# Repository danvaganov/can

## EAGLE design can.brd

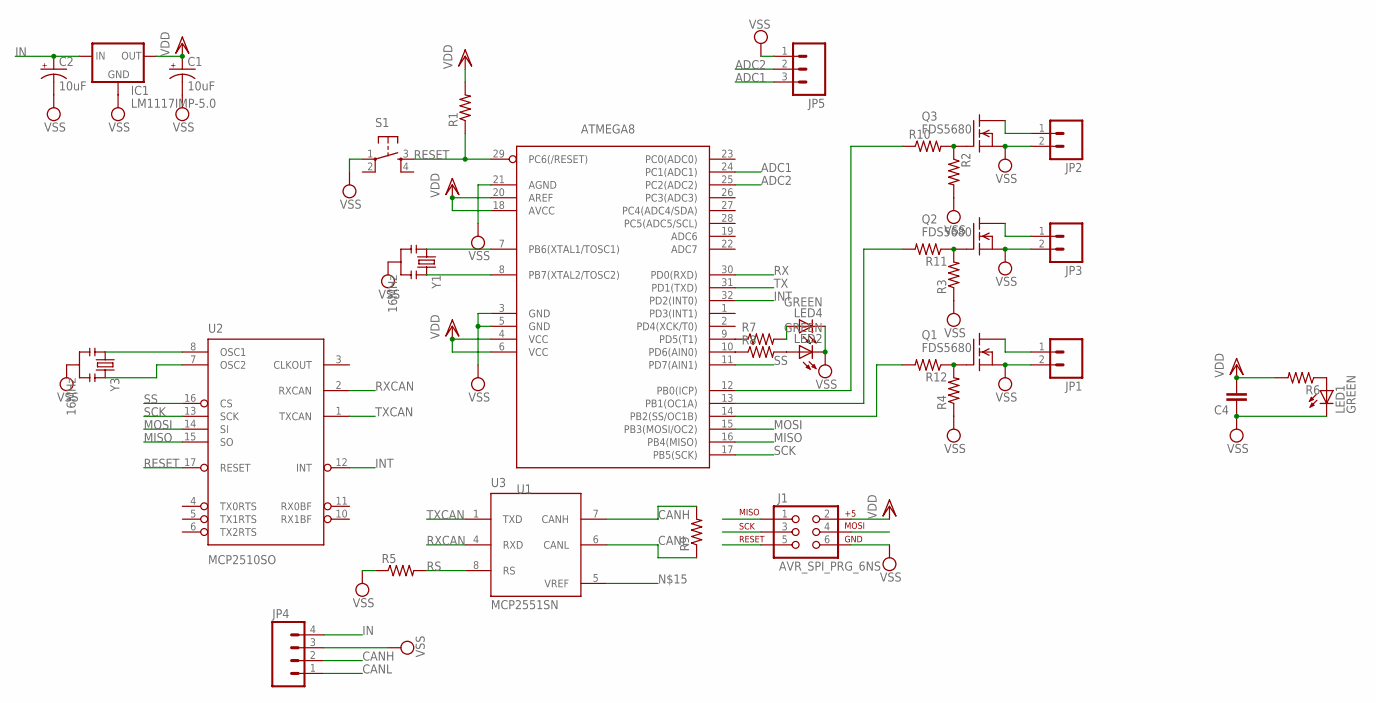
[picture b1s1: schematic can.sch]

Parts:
C1, C2: 10uF; EIA3216
C4: CAP1206; 1206
IC1: LM1117IMP-5.0; SOT223
J1: AVR_SPI_PRG_6NS; 2X3-NS
JP1, JP2, JP3: M02PTH; 1X02
JP4: M041X04_NO_SILK; 1X04_NO_SILK
JP5: M03PTH; 1X03
LED1, LED2, LED4: GREEN; LED-1206
Q1, Q2, Q3: FDS5680; SO-8
R1, R2, R3, R4, R5, R6, R9, R10, R11, R12: RESISTOR1206; 1206
R7, R8: RESISTOR0805-RES; 0805
S1: TAC_SWITCHSMD; TACTILE_SWITCH_SMD
U1: ATMEGA8; TQFP32-08
U2: MCP2510SO; SO-18W
U3: MCP2551SN; SO-08
Y1, Y3: 16MHz; RESONATOR-SMD

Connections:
ADC1: JP5.3, U1.24 (PC1(ADC1))
ADC2: JP5.2, U1.25 (PC2(ADC2))
CANH: JP4.2, R9.2, U3.7 (CANH)
CANL: JP4.1, R9.1, U3.6 (CANL)
IN: C2.A (+), IC1.3 (IN), JP4.4
INT: U1.32 (PD2(INT0)), U2.12 (INT)
MISO: J1.1, U1.16 (PB4(MISO)), U2.15 (SO)
MOSI: J1.4, U1.15 (PB3(MOSI/OC2)), U2.14 (SI)
unnamed: R8.1, U1.10 (PD6(AIN0))
unnamed: JP1.1, Q1.5 (D), Q1.6 (D), Q1.7 (D), Q1.8 (D)
unnamed: R7.1, U1.9 (PD5(T1))
unnamed: Q3.4 (G), R2.1, R10.2
unnamed: Q2.4 (G), R3.2, R11.1
unnamed: JP3.1, Q2.5 (D), Q2.6 (D), Q2.7 (D), Q2.8 (D)
unnamed: R12.2, U1.14 (PB2(SS/OC1B))
unnamed: JP2.1, Q3.5 (D), Q3.6 (D), Q3.7 (D), Q3.8 (D)
unnamed: Q1.4 (G), R4.2, R12.1
unnamed: R11.2, U1.13 (PB1(OC1A))
unnamed: R10.1, U1.12 (PB0(ICP))
unnamed: U1.7 (PB6(XTAL1/TOSC1)), Y1.1
unnamed: LED1.A, R6.1
unnamed: U1.8 (PB7(XTAL2/TOSC2)), Y1.3
unnamed: U2.8 (OSC1), Y3.1
unnamed: LED2.A, R8.2
unnamed: LED4.A, R7.2
unnamed: U2.7 (OSC2), Y3.3
RESET: J1.5, R1.1, S1.3, U1.29 (PC6(/RESET)), U2.17 (RESET)
RS: R5.2, U3.8 (RS)
RX: U1.30 (PD0(RXD))
RXCAN: U2.2 (RXCAN), U3.4 (RXD)
SCK: J1.3, U1.17 (PB5(SCK)), U2.13 (SCK)
SS: U1.11 (PD7(AIN1)), U2.16 (CS)
TX: U1.31 (PD1(TXD))
TXCAN: U2.1 (TXCAN), U3.1 (TXD)
VDD: C1.A (+), C4.2, IC1.2 (OUT), J1.2, R1.2, R6.2, U1.4 (VCC), U1.6 (VCC), U1.18 (AVCC), U1.20 (AREF), U2.18 (VDD), U3.3 (VDD)
VSS: C1.C (-), C2.C (-), C4.1, IC1.1 (GND), J1.6, JP1.2, JP2.2, JP3.2, JP4.3, JP5.1, LED1.C, LED2.C, LED4.C, Q1.1 (S), Q1.2 (S), Q1.3 (S), Q2.1 (S), Q2.2 (S), Q2.3 (S), Q3.1 (S), Q3.2 (S), Q3.3 (S), R2.2, R3.1, R4.1, R5.1, S1.1, U1.3 (GND), U1.5 (GND), U1.21 (AGND), U2.9 (VSS), U3.2 (VSS), Y1.2, Y3.2

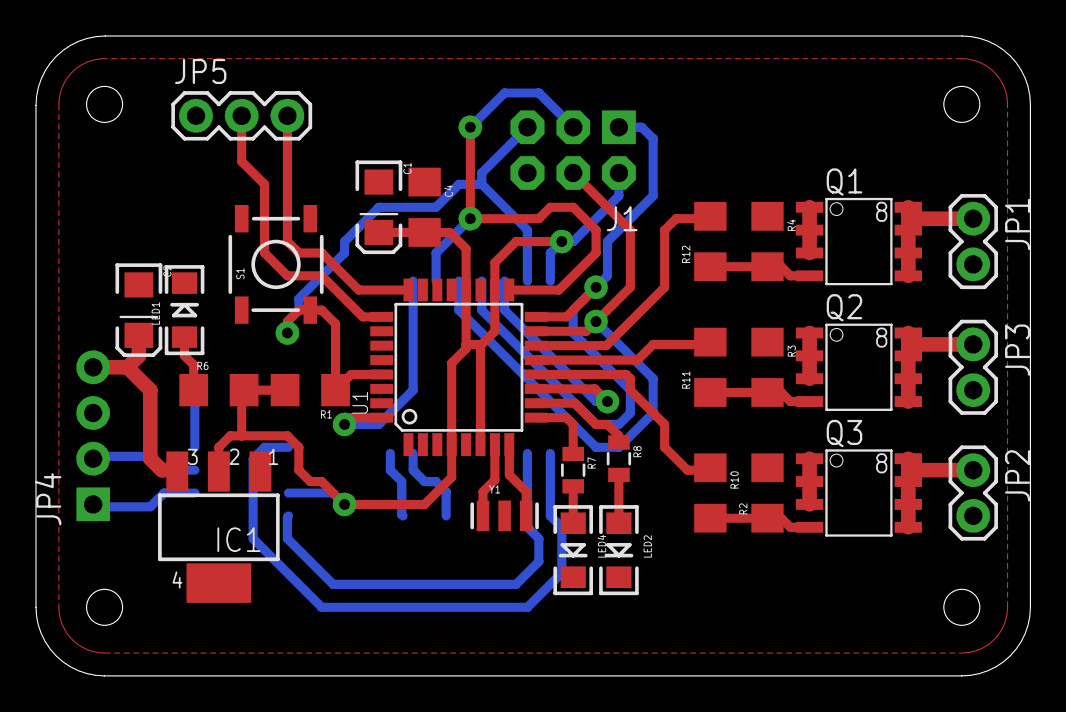
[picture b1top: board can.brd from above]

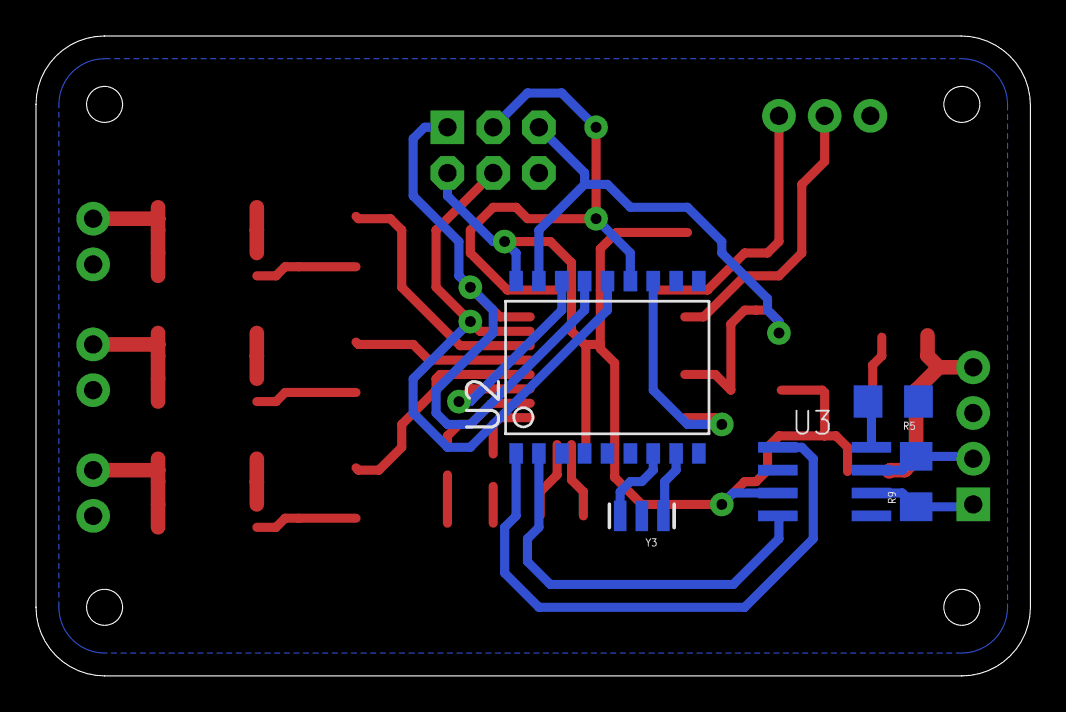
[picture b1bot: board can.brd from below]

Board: 2 copper layers, 55.2 x 35.5 mm, 34 parts (5 on the bottom side), 34 nets.

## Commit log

2014-08-16 init
2014-08-16 1.0.0
2014-09-17 1.0.1
2014-10-08 1.0.2

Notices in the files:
parts and their libraries:
SparkFun-Connectors: Licensing: CC v3.0 Share-Alike You are welcome to use this library for commercial purposes.
